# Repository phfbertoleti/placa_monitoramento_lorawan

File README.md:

# Placa - Monitoramento LoRaWAN / manutenção preventiva

Este é o repositório oficial da placa "Monitamento LoRaWAN" / placa "manutenção preventiva". Esta placa é um projeto open-source de minha autoria para monitamento de variáveis via LoRaWAN e para uso em algumas aplicações de manutenção preventiva. Este projeto faz uso do módulo Heltec wifi LoRa V1 (com conectividades LoRa/LoRaWAN, BLE e wi-fi).

## Princípio de funcionamento

Essa placa tem objetivo de facilitar o desenvolvimento de protótipos em Internet das Coisas, principalmente para aqueles focados em monitoramento remoto e manutenção preventiva. Para facilitar a montagem e uso, o Heltec wifi LoRa V1 e os módulos sensores são conectados em soquetes / barras de pinos do tipo fêmea. 
A placa suporta os seguintes módulos sensores:

* Módulo MPU6050
* Módulo BMP180

Ainda, a placa possui entrada digital (3.3V - 12V), que pode ser usada também para entradas pulsadas.

Quanto à alimentação, essa placa permite:
- Ser alimentada com bateria (LiPo ou Li-Ion, de 1 célula), com recarga por energias renováveis (7V - 12V), até 3 fontes diferentes de energias renováveis, desde que na mesma tensão.
- Ser alimentada por fonte 5V/2A via conector micro-USB.

Para facilitar o uso, a placa possui furação idêntica ao Arduino UNO. Dessa forma, fica mais simples projetar cases ou utilizar cases já fabricados.

## Funcionalidades

Esta placa, usada juntamente com um módulo Heltec wifi LoRa V1 e os sensores que a placa suporta, compreende as seguintes funcionaliades:
 
* Conectividades wifi, Bluetooth (BLE e clássico), LoRa e LoRaWAN.
* Medição de temperatura
* Medição de pressão barométrica
* Medição de aceleração (3 eixos)
* Giroscópio (3 eixos)
* Exibição de textos e imagens em display OLED 0.96" (azul)
* Recarga de bateria via energias renováveis

## O que está disponivel neste repositório?

Resposta curta: 100% do projeto. Ou seja:

* Projeto completo de hardware (feito no KiCad 5.1.5)
* Arquivos gerber, já nos padrões para fabricação exigidos pela JLCPCB (www.jlcpcb.com)
* Softwares de exemplo (todos feitos na Arduino IDE, fazendo uso de bibliotecas populares e consagradas)
* Lista de materiais (BOM)

Para ver a BOM interativa, [clique aqui](https://htmlpreview.github.io/?https://github.com/phfbertoleti/placa_monitoramento_lorawan/blob/master/Hardware/BOM/ibom.html)

## Desejo contribuir com novas funcionalidades ou correções. Sou bem vindo?

Claro. Sinta-se a vontade para contribuir com o projeto. Toda melhoria é bem vinda!

## Gostei do seu trabalho. Onde consigo mais coisas publicadas por você?

Visite meu [site pessoal](http://www.pedrobertoleti.com.br) para ter acesso a quase tudo que publico no Brasil e exterior.

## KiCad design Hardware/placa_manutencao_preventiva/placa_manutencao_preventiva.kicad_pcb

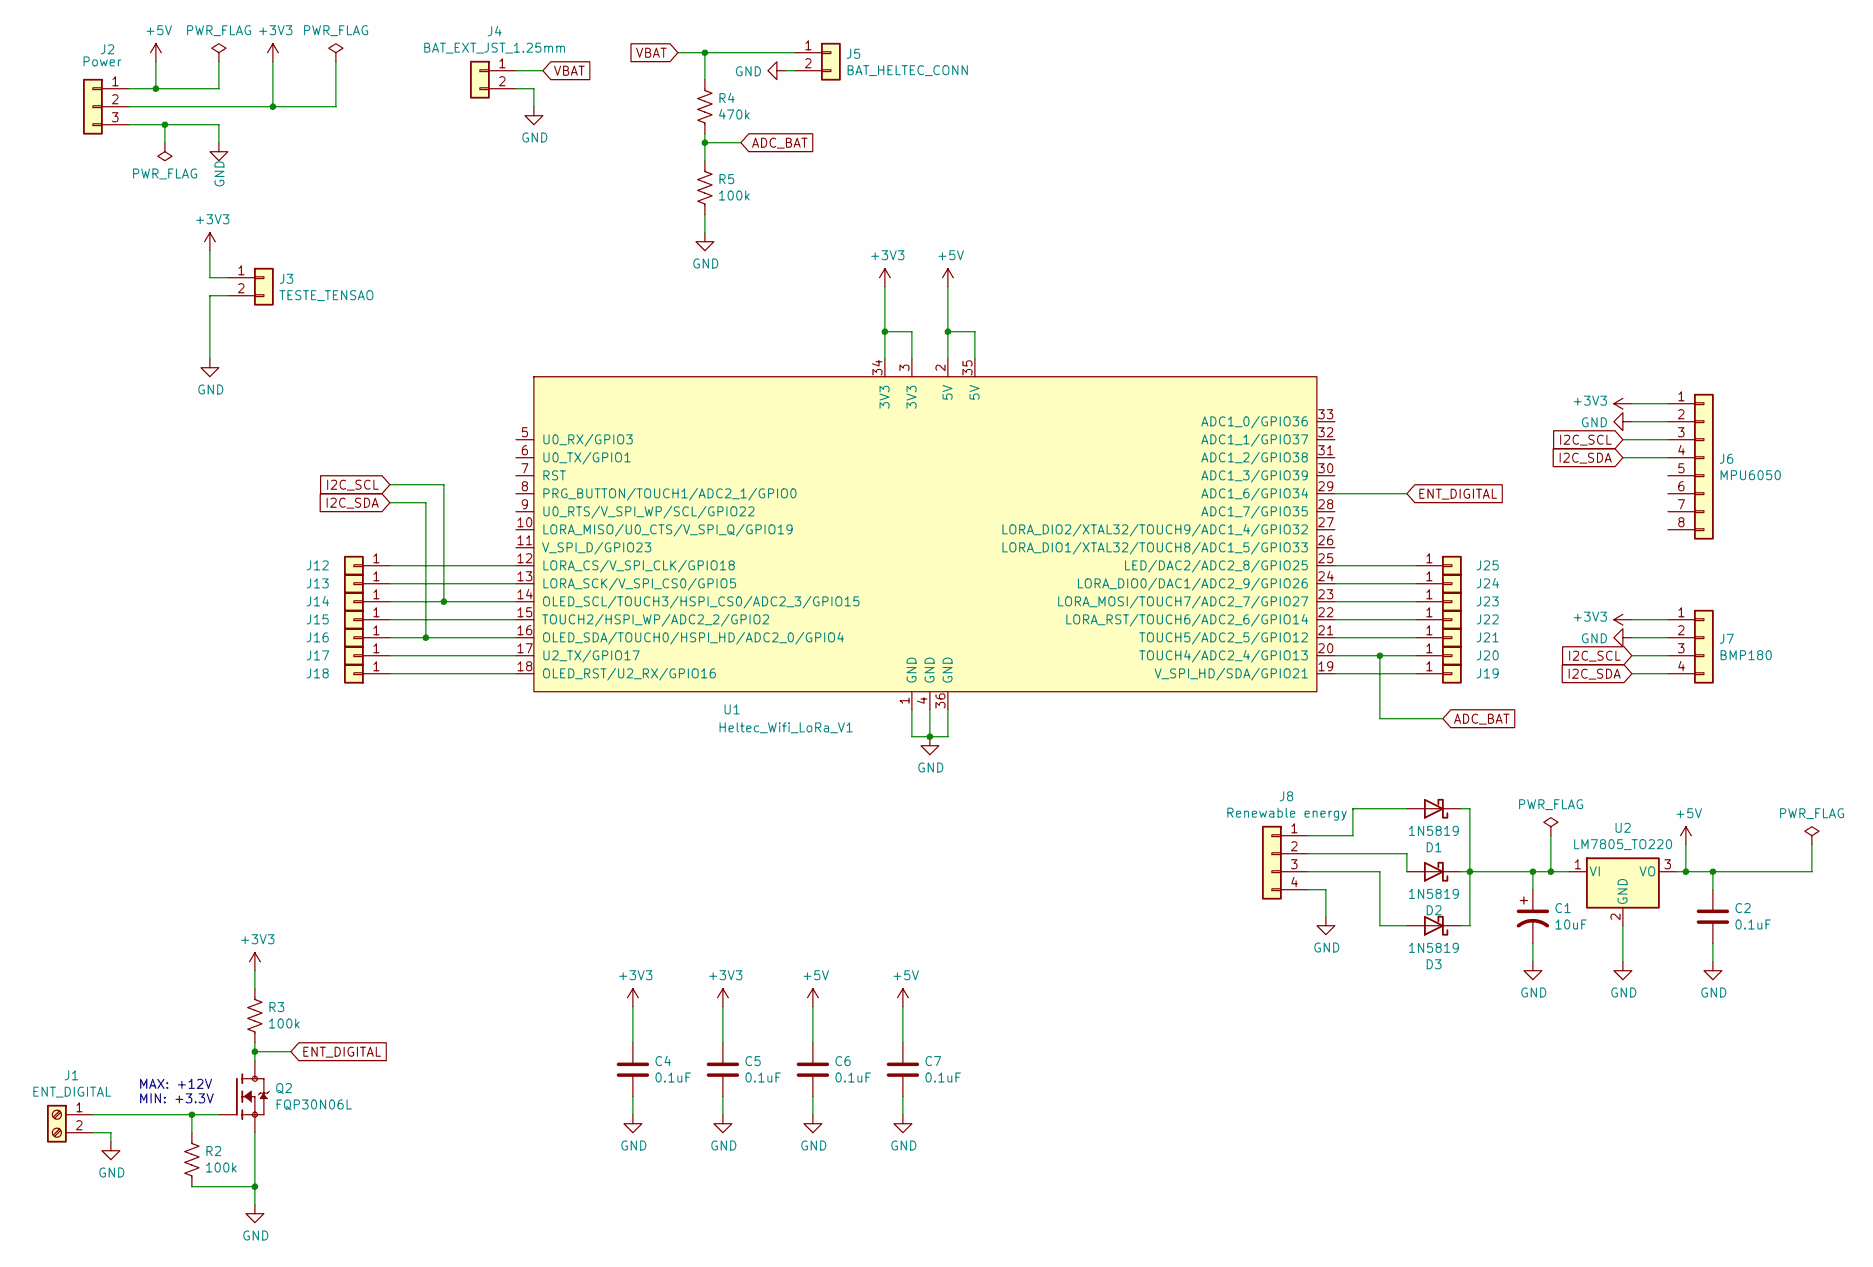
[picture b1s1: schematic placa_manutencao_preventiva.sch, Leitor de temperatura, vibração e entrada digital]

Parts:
C1: 10uF; CP_Radial_D5.0mm_P2.00mm
C2, C4, C5, C6, C7: 0.1uF; C_Disc_D5.1mm_W3.2mm_P5.00mm
D1, D2, D3: 1N5819; D_DO-41_SOD81_P10.16mm_Horizontal
J1: ENT_DIGITAL; PhoenixContact_MCV_1,5_2-G-5.08_1x02_P5.08mm_Vertical
J2: Power; PinHeader_1x03_P2.54mm_Vertical
J3: TESTE_TENSAO; TestPoint_2Pads_Pitch2.54mm_Drill0.8mm
J4: BAT_EXT_JST_1.25mm; PinHeader_1x02_P1.27mm_Vertical
J5: BAT_HELTEC_CONN; PinHeader_1x02_P2.54mm_Horizontal
J6: MPU6050; PinSocket_1x08_P2.54mm_Vertical
J7: BMP180; PinSocket_1x04_P2.54mm_Vertical
J8: Renewable energy; PinHeader_1x04_P2.54mm_Vertical
J12, J13, J14, J15, J16, J17, J18, J19, J20, J21, J22, J23, J24, J25: Conn_01x01; Pin_D0.9mm_L10.0mm_W2.4mm_FlatFork
Q2: FQP30N06L; TO220V
R2, R3, R5: 100k; R_Axial_DIN0207_L6.3mm_D2.5mm_P10.16mm_Horizontal
R4: 470k; R_Axial_DIN0207_L6.3mm_D2.5mm_P10.16mm_Horizontal
U1: Heltec_Wifi_LoRa_V1; Heltec_WiFi_LoRa_V1
U2: LM7805_TO220; TO-220-3_Vertical

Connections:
+3V3: C4.1, C5.1, J2.2, J3.1, J6.1, J7.1, R3.1, U1.3 (3V3), U1.34 (3V3)
+5V: C2.1, C6.1, C7.1, J2.1, U1.2 (5V), U1.35 (5V), U2.3 (VO)
ADC_BAT: J20.1, R4.2, R5.1, U1.20 (TOUCH4/ADC2_4/GPIO13)
ENT_DIGITAL: Q2.2, R3.2, U1.29 (ADC1_6/GPIO34)
GND: C1.2, C2.2, C4.2, C5.2, C6.2, C7.2, J1.2, J2.3, J3.2, J4.2, J5.2, J6.2, J7.2, J8.4, Q2.3, R2.2, R5.2, U1.1 (GND), U1.4 (GND), U1.36 (GND), U2.2 (GND)
I2C_SCL: J6.3, J7.3, J14.1, U1.14 (OLED_SCL/TOUCH3/HSPI_CS0/ADC2_3/GPIO15)
I2C_SDA: J6.4, J7.4, J16.1, U1.16 (OLED_SDA/TOUCH0/HSPI_HD/ADC2_0/GPIO4)
unnamed: C1.1, D1.1 (K), D2.1 (K), D3.1 (K), U2.1 (VI)
unnamed: D1.2 (A), J8.1
unnamed: D2.2 (A), J8.2
unnamed: D3.2 (A), J8.3
unnamed: J1.1, Q2.1, R2.1
unnamed: J12.1, U1.12 (LORA_CS/V_SPI_CLK/GPIO18)
unnamed: J13.1, U1.13 (LORA_SCK/V_SPI_CS0/GPIO5)
unnamed: J15.1, U1.15 (TOUCH2/HSPI_WP/ADC2_2/GPIO2)
unnamed: J17.1, U1.17 (U2_TX/GPIO17)
unnamed: J18.1, U1.18 (OLED_RST/U2_RX/GPIO16)
unnamed: J19.1, U1.19 (V_SPI_HD/SDA/GPIO21)
unnamed: J21.1, U1.21 (TOUCH5/ADC2_5/GPIO12)
unnamed: J22.1, U1.22 (LORA_RST/TOUCH6/ADC2_6/GPIO14)
unnamed: J23.1, U1.23 (LORA_MOSI/TOUCH7/ADC2_7/GPIO27)
unnamed: J24.1, U1.24 (LORA_DIO0/DAC1/ADC2_9/GPIO26)
unnamed: J25.1, U1.25 (LED/DAC2/ADC2_8/GPIO25)
VBAT: J4.1, J5.1, R4.1

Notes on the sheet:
MAX: +12V MIN: +3.3V

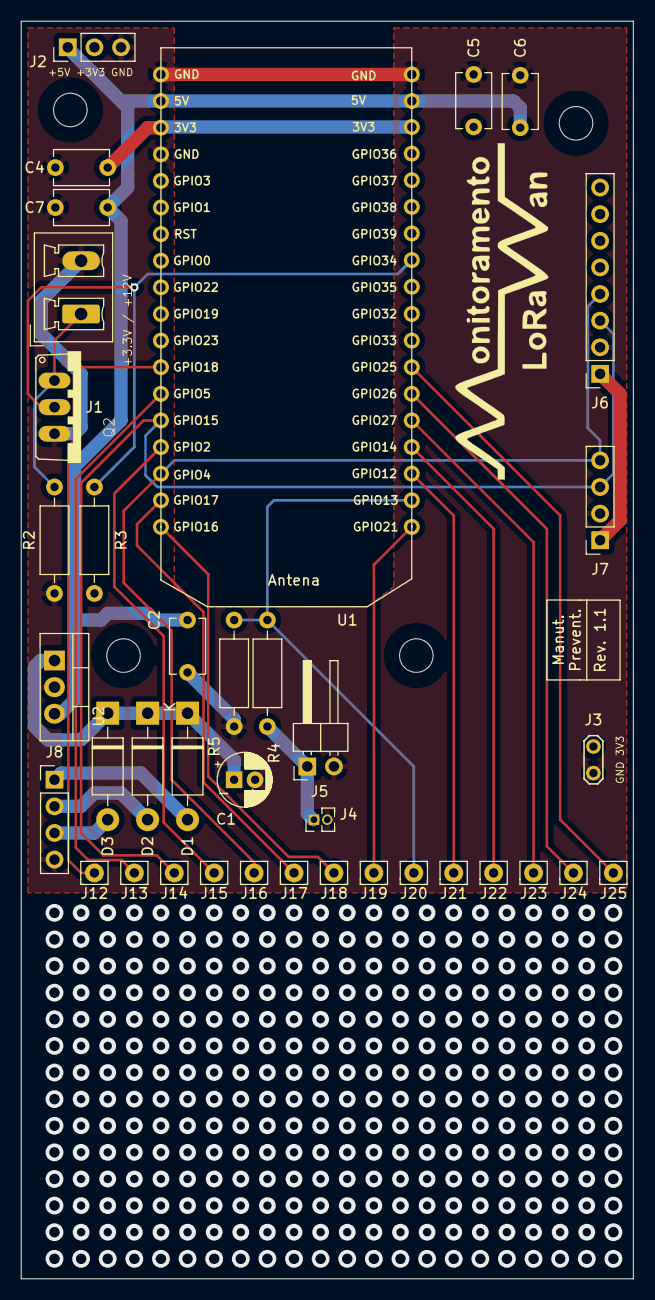
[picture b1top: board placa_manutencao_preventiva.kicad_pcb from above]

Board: 2 copper layers, 58.4 x 120.0 mm, 39 parts (0 on the bottom side), 24 nets.

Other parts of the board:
 : Arduino_UNO_R3_OnlyMountingHoles

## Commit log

2021-01-11 Primeiro commit
2021-01-11 Correções no readme
2021-03-22 Vers 1.1: Devolopment area
